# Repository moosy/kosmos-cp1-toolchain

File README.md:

# kosmos-cp1-toolchain
Toolchain for the 1980s Kosmos-CP1 learning computer.

This is a toolchain for owners of the brilliant Kosmos-CP1 learning computer.
See https://de.wikipedia.org/wiki/Kosmos_CP1 for details.
A comprehensive collection of documentation can be found at 
http://www.8bit-homecomputermuseum.at/computer/kosmos_computer_praxis_cp1.html.

**Firmware 6.x** for the AT28C256 (32 KB: four 2 KB blocks of own code, 99 projects in the flash, overlays with JOV,
random numbers with ZUF) runs in the CP1 since 2026-11-18 (6.22). The Pi tools in this root directory belong to 6.x.
Overview with block layout (German): [docs/firmware6-de.md](docs/firmware6-de.md), every routine with its address:
[docs/firmware6-routinen-de.md](docs/firmware6-routinen-de.md), quick reference 6.22 (German, 3 pages A4):
[cp1-schnelluebersicht-6.pdf](cp1-schnelluebersicht-6.pdf), sources: [firmware/v6/](firmware/v6/).

**Firmware 5.07** (AT28C64B, 256 flash banks) is described in the sections below; its quick reference is
[cp1-schnelluebersicht.pdf](cp1-schnelluebersicht.pdf), its Pi tools are kept in [firmware/v5/pi/](firmware/v5/pi/)
(`kosmos_schnell.py` is shared). The 6.x flash format is not compatible with 5.x.

Firmware internals, the terminal 7/8 protocol (K78P) with NIE and FNI, jobs and flash layout: [INTERNALS.md](INTERNALS.md)

Everything else of the project is here too:
- [firmware/](firmware/) - sources of the extended firmware 5.x and 6.x, own assembler, simulator and tests
  (the original ROM is copyrighted and not included; the build patches asig's `cp1.asm`)
- [hardware/](hardware/) - the EA adapter board (KiCad generator, board, Gerber, schematic)
- [docs/](docs/) - German project documentation (`firmware-de.md`, 6.x: `firmware6-de.md`) and the raw lab notebook (`laborbuch-de.md`)
- [examples/](examples/) - Rakete, Lauftext, Asteroiden, Minenflug (6.x: with dice rescue, overlay package); [cheatsheet/](cheatsheet/) - sources of the quick reference
- `kosmos-remote.service` - systemd unit for the web page

This toolchain consists of the following tools:

Firmware 5.07 in short
----------------------

*This and the following sections describe 5.07 (banks instead of projects). For 6.x see
[docs/firmware6-de.md](docs/firmware6-de.md) and the 6.x commands under "SPI flash" below.*

The CP1 runs an extended firmware (own code in the 8049's upper address range, two halves of
an AT28C64B switched by P1.4, see "SPI flash" below). At power-on it shows its version
(`5.07`) for one second. Since 5.00 the original cassette is gone: CAS and CAL operate the SPI
flash, and the Raspberry Pi talks to the CP1 over port 1 terminals 7 and 8 at any time.

Wiring to the Pi (both lines with the same protection; the Pi only ever pulls low):

```
GPIO: --------o-----[1 kOhm]------ Port 1/8   (Pin 37 = BCM 26: data / remote control)
              |                    Port 1/7   (Pin 35 = BCM 19: clock for fast transfers)
            -----,
              ^     Zener diode 3,3 V
             / \
            -----
              |
GND:  --------o-------------------- GND
```

Beware: The CP1 is a 5V device, therefore the voltage to the Raspberry Pi must be limited.

Two transfer modes:
- **NIE** (normal, interrupt enabled): small things in the background, unnoticed, also while a
  program runs: display and status, key presses, internal RAM, single memory cells.
- **FNI** (fast, no interrupt): whole banks or parts of them, from/to memory or flash. The CP1
  switches its interrupt off for about a second and shows the direction on the right three
  digits: `C-P` CP1 -> Pi, `P-C` Pi -> CP1, `F-P` flash -> Pi, `P-F` Pi -> flash, then `rdY`
  (or `Err`). FNI jobs only start while the CP1 waits for keys; otherwise they are refused.

Reset (firmware 5.02): hold **CLR and press STP** on the CP1, or `kosmos_remote.py reset` / the
"Reset" button on the web page (NIE command `09 00 00`). Works also while a program runs. Same as
switching off and on: all memory is cleared (8049 RAM and both 8155), then version, `P 000` and
autoboot if set.

Decimal point (hardware mod): the DP segments of all digits are connected and driven by PA7
of the 8155 (pin 28) through the former overvoltage BC238C. In normal operation the firmware
lights a separator dot after the third digit (`P  .000`); SEG programs can use it freely.

kosmos_send.py / kosmos_recv.py
-------------------------------

```
kosmos_send.py filename.json                   JSON -> CP1 memory (FNI, about 1 s)
kosmos_recv.py filename.json [--von N --bis M] CP1 memory -> JSON (without range: 000 to memory size)
```

No key press on the CP1 is needed. If the server `kosmos_remote.py serve` runs, both go
through it, otherwise they use the GPIOs directly. Same as `kosmos_remote.py laden/speichern`.

Older firmware:
- `--kassette`: the original slow cassette (original firmware up to 4.x; press CAS or CAL on
  the CP1). Uses GPIO 26 with gpiozero (1.x and 2.x). Receiving takes about 3.5 min (7 min
  with memory expansion); sending is faster (`time_base` 15 instead of the original 33).
- `--schnell`: the fast cassette of firmware 3.05-4.x (`kosmos_schnell.py`; bit = low pulse
  0.4 ms = 1 / 1.2 ms = 0, frame $C1, first cell, last cell, cells, CRC-8).

Remote control: kosmos_remote.py
--------------------------------

```
kosmos_remote.py serve [--port 8049]     web page + API (keeps GPIO 26 and 19)
kosmos_remote.py anzeige                 print the display
kosmos_remote.py taste 0 0 0 pc run      press keys (name[:ms], e.g. cas:1500)
kosmos_remote.py laden file.json         file -> memory (FNI)
kosmos_remote.py speichern file.json [--von N --bis M]   memory -> file (FNI)
kosmos_remote.py zelle N [B A]           read cell N, or set it to B.A (NIE, also while a program runs)
kosmos_remote.py reset                   cold start like power-on, all memory cleared (5.02)
```

Remote control is always on. The web page (http://bastelpi:8049/) shows the live display,
accumulator and PC, has a keyboard like the CP1's (keys are held as long as you hold them, so
"CAS 1 s" works), one program editor and a name table, shows and edits single cells (optionally
following them live while a program runs) and has a flash panel (directory, load, save, autoboot).

The editor holds one program: fetch it from the CP1 memory, from a flash bank ("In Editor" in the
directory) or from a .koa/.json file; change it; then "Assemblieren" (check, relabel), "In CP1
laden", "Editor speichern" (directly into a bank, memory untouched) or save it as .koa/.json.
The name table beside it ("035=display_loop") gives the disassembler speaking labels. When you
assemble, it is rebuilt from the labels in the source (plus your own entries for cells without a
label). With firmware 5.03 the table is stored in the flash bank together with the program and
comes back with "In Editor". In a .koa download it is appended as `// 035=name` comment lines,
which the editor reads back when opening the file. The draft stays in the browser.

The timing is done by `kosmos_rc` (C, built with `gcc -O2 -o kosmos_rc kosmos_rc.c`), which
drives and samples the GPIO registers through /dev/gpiomem; Python on a Pi Zero is too slow.
It needs real-time priority: run the server as a systemd service with
`AmbientCapabilities=CAP_SYS_NICE` (user in group gpio).

NIE protocol (terminal 8 = P1.7, handled in the CP1's timer interrupt every 2.56 ms):
- The Pi knocks by pulling the line low. 3.5 ms = status request: the CP1 sends internal RAM
  0x20..0x3A (display, key buffer, accumulator, PC, status), one byte per interrupt.
- 8.5 ms = command: 4 bytes follow, bit = low pulse 50 µs = 1 / 150 µs = 0, at least 50 µs
  high, LSB first; byte 4 = b1 ^ b2 ^ b3 ^ $A5. Replies: one byte per interrupt, low pulses
  ~50 / ~150 µs, then the check byte (XOR ^ $A5).
  - `01 zm dd` hold key: z = keyboard row (2..6), m = column mask, dd = frames of 15.36 ms
  - `02 aa nn` read nn bytes of internal RAM from aa; `03 aa ww` write internal RAM aa = ww
  - `04 jj 00` start job jj (attention). Reply = F_JOB: jj = accepted. For FNI jobs the
    acceptance is "terminal 7 goes low" instead.
  - `05 aa nn` / `06 aa nn` read nn bytes from byte address aa of the internal / CP3 8155,
    `07 aa ww` / `08 aa ww` write one byte (cell z = bytes 2z and 2z+1; CP3 = cells 128-255)
  - `09 00 00` reset like power-on (5.02, no reply)
- Key codes of the firmware: digit d = d + 1, OUT 11, INP 12, CAL 13, STEP 14, STP 15, RUN 16,
  CAS 17, CLR 18, PC 19, ACC 20; row = (code + 7) / 4, bit = (code + 7) % 4.

FNI protocol (interrupt off): terminal 7 = T (P1.6, clock), terminal 8 = D (P1.7, data).
- Per bit the Pi pulls T low (at least 80 µs); the CP1 holds T low as long as it is busy
  (erasing the flash may take a while). Then T is high for at least 100 µs. D low = 0, LSB first;
  the sender sets D, the CP1 polls T about every 22.5 µs (details in INTERNALS.md).
- Head [job, bank, first cell, count] + CRC-8, then blocks up to the next 4-cell boundary
  (2 bytes per cell) + CRC-8 (polynomial $07, init 0). After each block the receiver answers
  one bit: 1 = ok, 0 = repeat (3 tries on the CP1 side).
- Parameters, written with `03` before the `04`: F_BANK 0x2C, F_ANF 0x3C, F_ANZ 0x3D
  (0 = 256), F_START 0x3E (255 = no directory entry), name 0x60-0x6F. Result in F_JOB (0x26):
  0 = ok, $EE = error/refused.
- Jobs: $20 Pi -> memory, $21 memory -> Pi, $22 / $23 Pi -> flash (without / with name),
  $24 flash -> Pi, $25 whole bank -> Pi (256 cells, then 0x200-0x5FF of the sector: name,
  generation, valid, name table; 128 blocks of 8), $26 all names (per used bank a block
  [bank, 0, name 0-5], [name 6-13], [name 14-15]; end = block of 8 zeros), $29 Pi -> flash with
  name and name table (5.03: after the cell blocks 96 blocks of 8 for 0x300-0x5FF).
  The directory is read with $24 of bank 0 plus $26.
- Jobs with interrupt on: $04 load bank, $08 autoboot, $80/$81 memory -> bank (with name).
  ($01 raw read and $10 find bank were dropped in 5.03.)

SPI flash ("hard disk")
-----------------------

Firmware 6.x (root directory tools):

```
kosmos_remote.py flash                         project directory (number, banks, name, short display, autoboot)
kosmos_remote.py flash-speichern 12 "Rakete" [--start 20]   CP1 memory -> project 12 (new: the CP1 creates it)
kosmos_remote.py flash-laden 12                project 12 -> memory, PC = start
kosmos_remote.py autoboot 12                   start project 12 at power-on (0 = off)
kosmos_remote.py projekt-sichern 12 x.cp1      whole project (all banks, labels, pictures) -> file; alle-sichern dir/
kosmos_remote.py projekt-einspielen x.cp1 [12] file -> project (empties unused reserved banks, 6.22)
kosmos_remote.py projekt-loeschen 12           remove project 12 from the directory
kosmos_remote.py paket spiel.koa spiel.cp1     source (also overlay package) -> project file
kosmos_remote.py bank-leeren 6 [7 ...]         empty banks (6.22; banks 0-3 only with --auch-system)
```

Firmware 5.07 (tools in firmware/v5/pi/):

```
kosmos_remote.py flash                         directory (bank, start, name, autoboot)
kosmos_remote.py flash-speichern 12 "Rakete" [--start 20]   CP1 memory -> bank 12
kosmos_remote.py flash-laden 12                bank 12 -> memory, PC = start
kosmos_remote.py autoboot 12                   start bank 12 at power-on (0 = off)
kosmos_remote.py bank-sichern 12 file.json     bank 12 -> file directly (memory untouched; names -> file.json.namen)
kosmos_remote.py bank-einspielen 12 file.json ["Name"] [--start 20] [--namen file.namen]   file -> bank 12 directly
```

Hardware: an IS25LP016D (2 MB, 3.3 V) on port 1 terminals 1-4: P1.0 = CS#, P1.1 = SCK,
P1.2 = SI, P1.3 = SO. Supply from 5 V via 56 Ohm and a 3.3 V Zener diode (plus 10 µF and
100 nF); CS#, SCK and SI through 4.7 kOhm each (the flash's clamp diodes take the excess, the
Zener absorbs the current), SO through 1.5 kOhm to the 8049. WP# and HOLD# to 3.3 V.

The firmware no longer fits into 4 KB, so it uses both halves of the AT28C64B: **A12 is
driven by P1.4** (pin 31 of the 8049; on the adapter, cut the trace to terminal 5 and wire the
CPU side to the middle pin of JP3, jumper removed). Both halves contain the same lower 2 KB
(original code, interrupt, remote control); the upper 2 KB of half A (A12 = 1, EEPROM
0x1000-0x1FFF, selected after reset) hold the key handling and extensions, those of half B
(EEPROM 0x0000-0x0FFF) the flash and FNI code. Switching happens in small stubs at the same
address in both halves (`ANL/ORL P1,#$10`). `OUT P1A` keeps P1.0-P1.4 and P1.6/P1.7 at 1, so
programs can only use terminal 6 of port 1.

Storage: 256 banks of 256 cells (512 bytes). Each bank uses two 4 KB sectors alternately:
writing erases the free sector, copies the old contents over in 8-byte pieces, inserts the new
cells and finally marks the sector valid (generation counter), so a power failure never loses
the old version. Bank 0 is the directory: cell 0 = (00, autoboot bank), cell n = (00, start
of bank n). Name (16 ASCII characters) and generation are stored behind the cells.
Firmware 5.03: 0x300-0x5FF of the sector hold the name table (5.05: the last 8 bytes, 0x5F8-0x5FD, are the
bank's own 6-digit display for browsing) (per entry: length, cell, name in
ASCII; FF = end; 768 bytes, about 70 names of 8 characters). Byte 0x212 = 00 marks a bank with
names. Only then the copy runs up to 0x5FF (about 1.7 s longer), otherwise it stops at 0x217
as before.

On the CP1 (always 3 digits; CLR clears the input, STP aborts):
- CAS short: `bAn ___`, type nnn, CAS: memory -> bank nnn, start = current PC (set it first
  with `xxx PC`). Display `5to rdY`.
- CAS held 1 s: `Fr ___`, `to ___` (cells of memory), `bAn ___`, `d5t ___` (first cell in the
  bank), each confirmed with CAS. Only pressing CAS takes the default (whole memory, cell 0).
  The rest of the bank stays, the directory is not touched.
- CAL short (5.05): browse the used banks. Each shows `bAn nnn` for a moment, then its own 6-digit
  display (set on the web page, field "Anzeige") or the first letters of its name. CAL again = next
  bank (after the last one it starts again; that step takes ~1.6 s), hold CAL 1 s = load it (PC = start,
  `P xxx`; RUN starts it), digits = the usual `bAn ___` input, STP = cancel.
- CAL held 1 s: `bAn ___`, `Fr ___`, `to ___` (cells in the bank), `d5t ___` (cells of
  memory). PC stays, display `LdA rdY`.
- RUN held 1 s: `bot ___`, nnn RUN: autoboot bank nnn (`bot rdY`), `000` = off. At power-on
  the CP1 shows `bot nnn` for 2 s (any key aborts), then loads and runs the bank.
- Errors: F-010 no flash answers, F-011 bank empty, F-003 bank 0 / invalid range, F-001 not
  3 digits.

New commands (firmware 4.01), parameters on the JSR/PSH stack:
- `36 PSK xxx` push the constant xxx
- `37 FRD xxx` pop count (0 = 256), first cell in the bank, bank; read these cells into memory from xxx
- `38 FWR xxx` the same in the other direction
- bank 000 (firmware 5.07) = the program's own bank, i.e. the bank it was loaded from (no own bank: F-003)
- missing stack values -> F-009, no flash -> F-010
- `39 TSE 000` (firmware 4.02): accumulator = digit pressed since the last TSE, else 255; does not wait.
  VZG now remembers digit keys pressed while it waits, so a game loop with VZG + TSE never misses a key.

```
PSK 5      ; bank
PSK 123    ; first cell in the bank
PSK 10     ; 10 cells
FRD 80     ; -> memory 80..89
```

```
PSK 0      ; own bank (5.07)
PSK leben  ; first variable
PSK 16     ; 16 cells
FRD leben  ; -> all start values back, e.g. for a new game (4 cells instead of one AKO/ABS pair each)
```

Firmware 5.06: commands with a fixed value and pictures from flash
- `40`–`46`: `ADD #n`, `SUB #n`, `VGL #n`, `VGR #n`, `VKL #n`, `UND #n`, `ODR #n` – like the normal
  commands, but n is the value itself instead of a cell (no constant cells needed any more).
- `47 SEF xxx`: show 6 picture bytes from the program's own bank (stored in the flash sector, not in
  the 256 cells). Pictures are defined on the web page (field "Bilder", e.g. `titel=MInEn`,
  `lauf=  HALLO CP1  `, `#1,2,3` for raw segment values) and written with "Editor speichern"; in the
  program you write `SEF titel`, `SEF lauf+3` or `ADD #lauf` – the assembler fills in the numbers.
  `SEF 254` takes the position from the accumulator (scrolling text in a loop), `SEF 248` shows the
  bank's own browse display, `SEF 255` clears. About 12 ms per picture.
- The JSR/PSH stack has 23 levels since 5.06.

Example: `examples/minenflug.koa` – a little game with mines, shots, LED bars on ports 2 and 4 and
pictures (bank 8 on Michael's CP1). Details of all commands and data formats: [INTERNALS.md](INTERNALS.md).

Demos: `8 RUN` reaction test, `9 RUN` countdown.

kosmos_json_show.py filename.json
---------------------------------

Displays the contents of the JSON file in a decent way and shows the opcodes.

kosmos_disasm.php [-i] [-c] [-d] [-o] [-n names.txt] filename.json
-----------------------------------------------------------------

Disassembles the JSON file and creates a KOA assembly language file.

Options:

```
       -c show code
       -d show description
       -i show inline numerics
       -o create filename.koa
       -n name table: one "035=display_loop" per line; these names are used instead of
          label_N / wert_N, and every named cell gets a label (even if nothing refers to it)
```

Every label line shows the cell number it stands for (`>display_loop:          035`). It is
only for reading: the assembler ignores everything behind the label and writes the current
number again with `-r` (relabel), so moving code never causes a conflict.

By default kosmos_disasm displays only the assembly tokens and the labels it has
has recognized. Line numbers are omitted if possible:

```
user@machine:# kosmos_disasm.php lichtband.json

>label_1:

  001 LIA adresse_1
      ABS wert_4
      AKO 255
      SUB wert_4
      P2A 000
      VZG 030
      LDA adresse_1
      VGL wert_2
      SPB label_2
      ADD wert_1
      ABS adresse_1
      SPU label_1

>label_2:
      SUB wert_1
      ABS adresse_1
      VGL wert_3
      [...]

```
With the option -c you may additionally view the decimal codes entered in the CP1 
including all line numbers.

```
user@machine:# kosmos_disasm.php lichtband.json -c

>label_1:

  001 LIA adresse_1           |  001: 19.067
      ABS wert_4              |  002: 06.070
      AKO 255                 |  003: 04.255
      SUB wert_4              |  004: 08.070
      P2A 000                 |  005: 18.000
      VZG 030                 |  006: 03.030
      LDA adresse_1           |  007: 05.067
      VGL wert_2              |  008: 10.068
      SPB label_2             |  009: 11.013
      ADD wert_1              |  010: 07.051
      ABS adresse_1           |  011: 06.067
      SPU label_1             |  012: 09.001

>label_2:
      SUB wert_1              |  013: 08.051
      ABS adresse_1           |  014: 06.067
      VGL wert_3              |  015: 10.069
      [...]

```

With the -d option you can display the explanation for each command.
In the near future there may also be an English version for this:

```
user@machine:# kosmos_disasm.php lichtband.json -c -d

>label_1:

  001 LIA adresse_1           |  001: 19.067  |  Akku mit Inhalt der Zelle laden, deren Adresse unter 67 (adresse_1) steht
      ABS wert_4              |  002: 06.070  |  Akku-Inhalt in Zelle 70 (wert_4) speichern
      AKO 255                 |  003: 04.255  |  Konstante 255 in den Akku laden
      SUB wert_4              |  004: 08.070  |  Vom Akku Inhalt von Zelle 70 (wert_4) subtrahieren
      P2A 000                 |  005: 18.000  |  Akku-Inhalt an Klemme 0 von Port 2 legen (000 = alle)
      VZG 030                 |  006: 03.030  |  Verzögern um 30 ms
      LDA adresse_1           |  007: 05.067  |  Inhalt von Zelle 67 (adresse_1) in den Akku laden
      VGL wert_2              |  008: 10.068  |  Prüfen, ob Akku gleich Inhalt von Zelle 68 (wert_2) ist
      SPB label_2             |  009: 11.013  |  Wenn ja, springe zu Adresse 13 (label_2)
      ADD wert_1              |  010: 07.051  |  Zum Akku Inhalt von Zelle 51 (wert_1) addieren
      ABS adresse_1           |  011: 06.067  |  Akku-Inhalt in Zelle 67 (adresse_1) speichern
      SPU label_1             |  012: 09.001  |  Springe zu Adresse 1 (label_1)

>label_2:
      SUB wert_1              |  013: 08.051  |  Vom Akku Inhalt von Zelle 51 (wert_1) subtrahieren
      ABS adresse_1           |  014: 06.067  |  Akku-Inhalt in Zelle 67 (adresse_1) speichern
      VGL wert_3              |  015: 10.069  |  Prüfen, ob Akku gleich Inhalt von Zelle 69 (wert_3) ist
      [...]

```

The -o option writes the disassembled text to a KOA assembly language file.

kosmos_asm.php [-i] [-c] [-d] [-o] [-s] [-r] filename.koa
---------------------------------------------------------

Options:  
```          
          -c show code
          -d show description
          -i show inline numerics
          -o create filename.json
          -s create filename.json and start transfer to CP1
          -r rewrite (beautify) input file
```

This is the CP1 assembler. You can simply start with the CP1 mnemonics and use either numeric or symbolic parameters.
If you use symbolic parameters, you must declare them somewhere with a leading '>'.

You don't have to specify line numbers, if you do the assembler will try to assign them as you specified them.
Data values are marked with the mnemonic '#'.

Example:

```
AKO 0
>loop:
ANZ
VZG 250
ADD one
SPU loop

>one:
# 1
```

If you call the kosmos_asm.php it will output this:

```
user@machine:# kosmos_asm.php example.koa

      AKO 000

>loop:
      ANZ
      VZG 250
      ADD one
      SPU loop

>one:
      # 001
```

As you can see, the assembler has beautified your code. You don't see any assembled code because you neither told the assembler
assembler neither to display it nor to write it to a file. 

With the -c option, you can see the code:

```
user@machine:# kosmos_asm.php example.koa -c
      AKO 000                 |  000: 04.000

>loop:
      ANZ                     |  001: 02.000
      VZG 250                 |  002: 03.250
      ADD one                 |  003: 07.005
      SPU loop                |  004: 09.001

>one:
      # 001                   |  005: 00.001
```

If you add the -d option, you will get a (German) explanation for each command:

```
user@machine:# kosmos_asm.php example.koa -c -d

      AKO 000                 |  000: 04.000  |  Konstante 000 in den Akku laden

>loop:
      ANZ                     |  001: 02.000  |  Akku-Inhalt anzeigen
      VZG 250                 |  002: 03.250  |  Verzögern um 250 ms
      ADD one                 |  003: 07.005  |  Zum Akku Inhalt von Zelle 005 (one) addieren
      SPU loop                |  004: 09.001  |  Springe zu Adresse 001 (loop)

>one:
      # 001                   |  005: 00.001  |  Datenwert 001

```

You can see the real values of the symbolic constants and the line number in the code section.
Alternatively, you can tell the assembler to display them inline with the -i option:

```
user@machine:# kosmos_asm.php example.koa -i

 (000) AKO 000

>loop:
 (001) ANZ
 (002) VZG 250
 (003) ADD one (005)
 (004) SPU loop (001)

>one:
 (005) # 001

```

Line numbers in parentheses are automatically assigned by the assembler.

If you like the beautified output, you can use the -r option to rewrite your source file with the beautified version.
The beautified output (and -r) puts the current cell number behind every label, so you see where things landed.
Several labels in a row all name the same cell.

Note: You can add comments by starting a line with '//'. These comments will be preserved by the assembler.
You can also add comments at the end of any line that starts with '//', but these will be retained in the
beautified output. It is recommended to use your own comment lines for this reason.

With the -o option you can instruct the assembler to write a JSON file for further use, e.g. for writing
to the CP1. If you use the option -s, the tool kosmos_send.py is called automatically and the transfer to the CP1 begins.

Installation and Prerequisites
------------------------------

The installation is pretty straightforward: just copy the files to any location in the file system of your Raspberry Pi
(recommended: /usr/local/bin) and set the execution flags (e.g. with chmod +x *.php *.py).
If you don't use /usr/local/bin, you should change the path at the end of the
of kosmos_asm.php:

```
if ($send) passthru("/usr/local/bin/kosmos_send.py $fo");
                     ^^^^^^^^^^^^^^^
```

The default Raspberry Pi operating system (formerly Raspbian, a Debian derivative) should include everything you need, perhaps with the exception of the php package
which has to be installed manually:

```
user@machine:# sudo apt update
user@machine:# sudo apt install php -y
```

For the remote control, build the timing helper and run the server as a service:

```
user@machine:# gcc -O2 -o kosmos_rc kosmos_rc.c
```

```
# /etc/systemd/system/kosmos-remote.service
[Unit]
Description=Kosmos CP1 remote control (web page port 8049)
After=network-online.target

[Service]
User=pi
SupplementaryGroups=gpio
WorkingDirectory=/home/pi/kosmos-cp1-toolchain
ExecStart=/usr/bin/python3 /home/pi/kosmos-cp1-toolchain/kosmos_remote.py serve
AmbientCapabilities=CAP_SYS_NICE
CapabilityBoundingSet=CAP_SYS_NICE
NoNewPrivileges=true
Restart=on-failure

[Install]
WantedBy=multi-user.target
```

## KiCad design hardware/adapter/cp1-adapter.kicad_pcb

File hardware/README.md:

# EA adapter (hardware)

Adapter board that lets the CP1's 8049 run its code from an external EEPROM (EA high): the original
8049 stays in its socket on the adapter, the AT28C64B holds the (extended) firmware.

| File | Content |
|---|---|
| `adapter/cp1adapter.py` | generates the KiCad board (placement, netlist, own grid router, GND fills) – run with KiCad's Python |
| `adapter/cp1schaltplan.py` | generates the schematic (`schaltplan.svg` / `.pdf`) |
| `adapter/cp1-adapter.kicad_pcb` | the board (v1, produced at NextPCB) |
| `adapter/cp1-adapter-gerber.zip` | Gerber files as ordered |
| `adapter/top.png` | rendering of the top side |
| `cp1-stecker-dioden.png` | fix on the plug board: 4 × BAT42 in P20–P23 (keyboard columns must not pull A8–A11 high) |

Changes made after v1 (see `../docs/firmware-de.md` for details and photos of the reasoning):
- **remove C1** (22 pF at XTAL1) – the NMOS MCS-48 oscillator does not tolerate it;
- 4 × BAT42 in the keyboard column lines (picture above);
- jumper JP2 replaced by a wire A11 → P23 (4 KB address space);
- trace from pin 31 (P1.4) to terminal 5 cut, P1.4 drives A12 of the EEPROM (two 4 KB halves);
- SPI flash IS25LP016D on terminals 1–4, Pi on terminals 7/8 (see `../INTERNALS.md`).

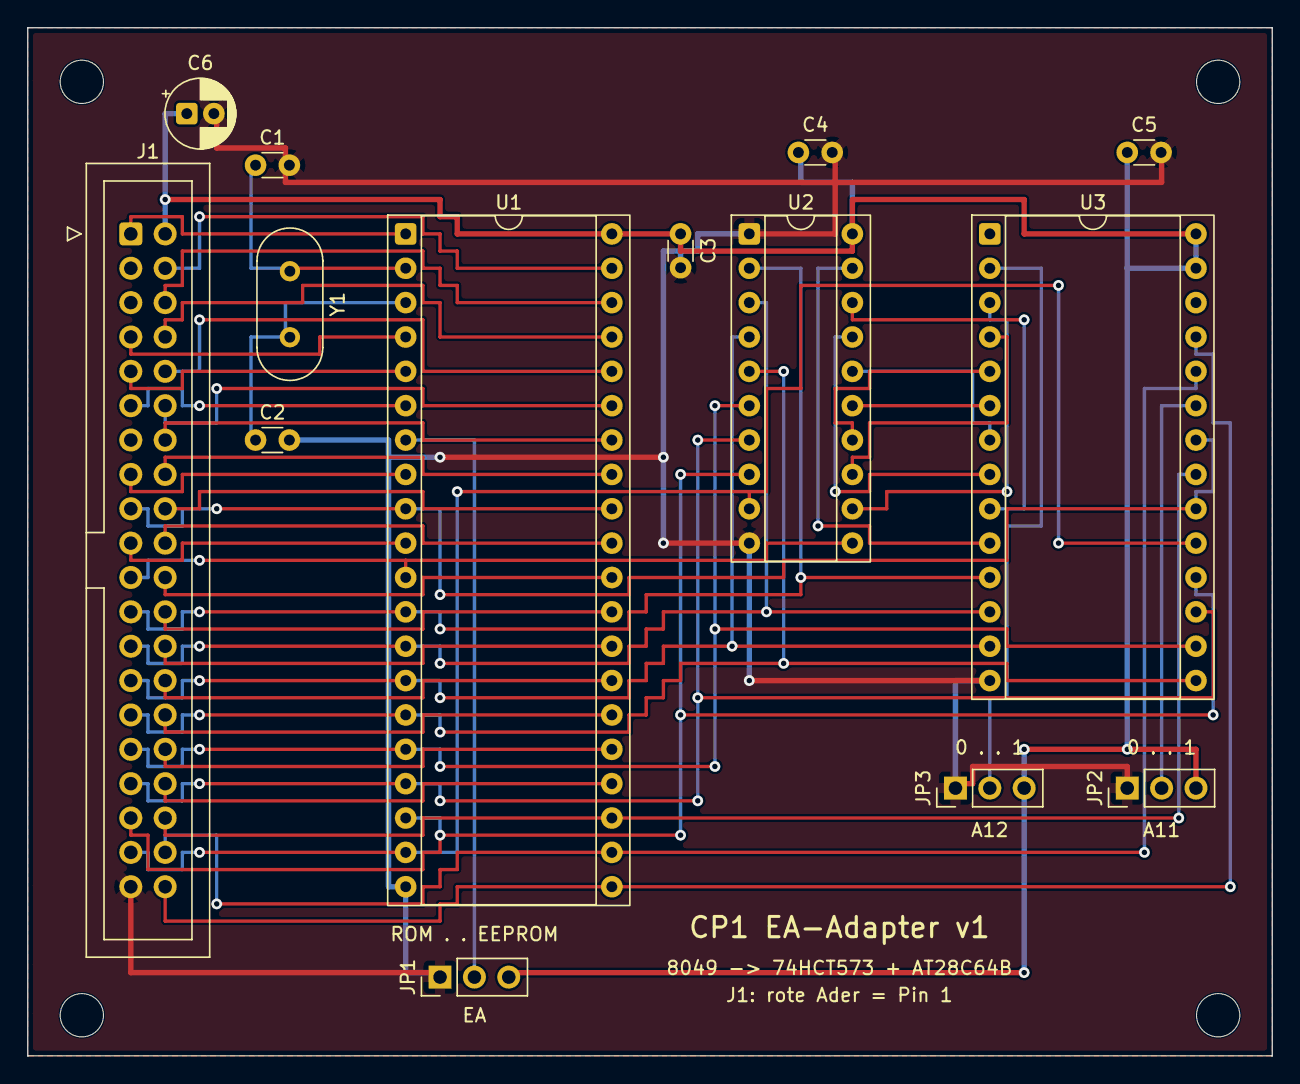
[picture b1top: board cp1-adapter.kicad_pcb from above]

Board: 2 copper layers, 92.0 x 76.0 mm, 18 parts (0 on the bottom side), 50 nets.

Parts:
C1, C2: 22p; C_Disc_D3.0mm_W1.6mm_P2.50mm
C3, C4, C5: 100n; C_Disc_D3.0mm_W1.6mm_P2.50mm
C6: 10µ; CP_Radial_D5.0mm_P2.00mm
H1, H2, H3, H4: MountingHole_3.2mm_M3
J1: zum CP1 (Flachband); IDC-Header_2x20_P2.54mm_Vertical
JP1: EA; PinHeader_1x03_P2.54mm_Vertical
JP2: A11; PinHeader_1x03_P2.54mm_Vertical
JP3: A12; PinHeader_1x03_P2.54mm_Vertical
U1: 8049 (ZIF-40); DIP-40_W15.24mm_Socket
U2: 74HCT573; DIP-20_W7.62mm_Socket
U3: AT28C64B; DIP-28_W15.24mm_Socket
Y1: 6 MHz; Crystal_HC49-4H_Vertical

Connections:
/INT: J1.11, U1.6
/PSEN: J1.17, U1.9, U3.20, U3.22
/RD: J1.15, U1.8
/RESET: J1.7, U1.4
/SS: J1.9, U1.5
/WR: J1.19, U1.10
A11: JP2.2, U3.23
A12: JP3.2, U3.2
ALE: J1.21, U1.11, U2.11
DB0: J1.23, U1.12, U2.2, U3.11
DB1: J1.25, U1.13, U2.3, U3.12
DB2: J1.27, U1.14, U2.4, U3.13
DB3: J1.29, U1.15, U2.5, U3.15
DB4: J1.31, U1.16, U2.6, U3.16
DB5: J1.33, U1.17, U2.7, U3.17
DB6: J1.35, U1.18, U2.8, U3.18
DB7: J1.37, U1.19, U2.9, U3.19
EA: JP1.2, U1.7
GND: C1.2, C2.2, C3.2, C4.2, C5.2, C6.2, J1.39, JP1.1, JP2.1, JP3.1, U1.20, U2.1, U2.10, U3.14
LA0: U2.19, U3.10
LA1: U2.18, U3.9
LA2: U2.17, U3.8
LA3: U2.16, U3.7
LA4: U2.15, U3.6
LA5: U2.14, U3.5
LA6: U2.13, U3.4
LA7: U2.12, U3.3
P10: J1.28, U1.27
P11: J1.26, U1.28
P12: J1.24, U1.29
P13: J1.22, U1.30
P14: J1.20, U1.31
P15: J1.18, U1.32
P16: J1.16, U1.33
P17: J1.14, U1.34
P20: J1.40, U1.21, U3.25
P21: J1.38, U1.22, U3.24
P22: J1.36, U1.23, U3.21
P23: J1.34, U1.24
P24: J1.12, U1.35
P25: J1.10, U1.36
P26: J1.8, U1.37
P27: J1.6, U1.38
PROG: J1.32, U1.25
T0: J1.1, U1.1
T1: J1.4, U1.39
VCC: C3.1, C4.1, C5.1, C6.1, J1.2, JP1.3, JP2.3, JP3.3, U1.40, U2.20, U3.27, U3.28
VDD: J1.30, U1.26
XTAL1: C1.1, U1.2, Y1.1
XTAL2: C2.1, U1.3, Y1.2
